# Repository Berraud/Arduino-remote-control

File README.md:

# Arduino-remote-control
Arduino based multi channel remote control for aeromodelism with telemetry and PS2 controller.
Based on arduino pro mini and NRF20L01 modules. Uses a PS2 remote controller as input.
Features multiple channels and memory for saving multiple models. Dual rates, throttle cut, on-fly default position set up (in case of signal lost), telemetry for measuring remote battery voltage and some other things.
If you have any questions email me to simonb2230@gmail.com

Based on a few nice projects from:
http://www.billporter.info/2010/06/05/playstation-2-controller-arduino-library-v1-0/
https://www.flitetest.com/articles/custom-arduino-2-4ghz-rc-transmitter
http://www.electronoobs.com/eng_robotica_tut5_2_1.php

and probably some other examples that I can't remember.

The power for the remote is from a single LiIon battery from a portable charger (using the same charging circuit)
The power for the receiver comes from the BEC of the ESC. The resistive divider on the receiver is calculated for a 3S Lipo battery.

The NRF modules need a 1uf ceramic SMD cap soldered directly on the PCB of the module itself

The range tested on ground is about 800m

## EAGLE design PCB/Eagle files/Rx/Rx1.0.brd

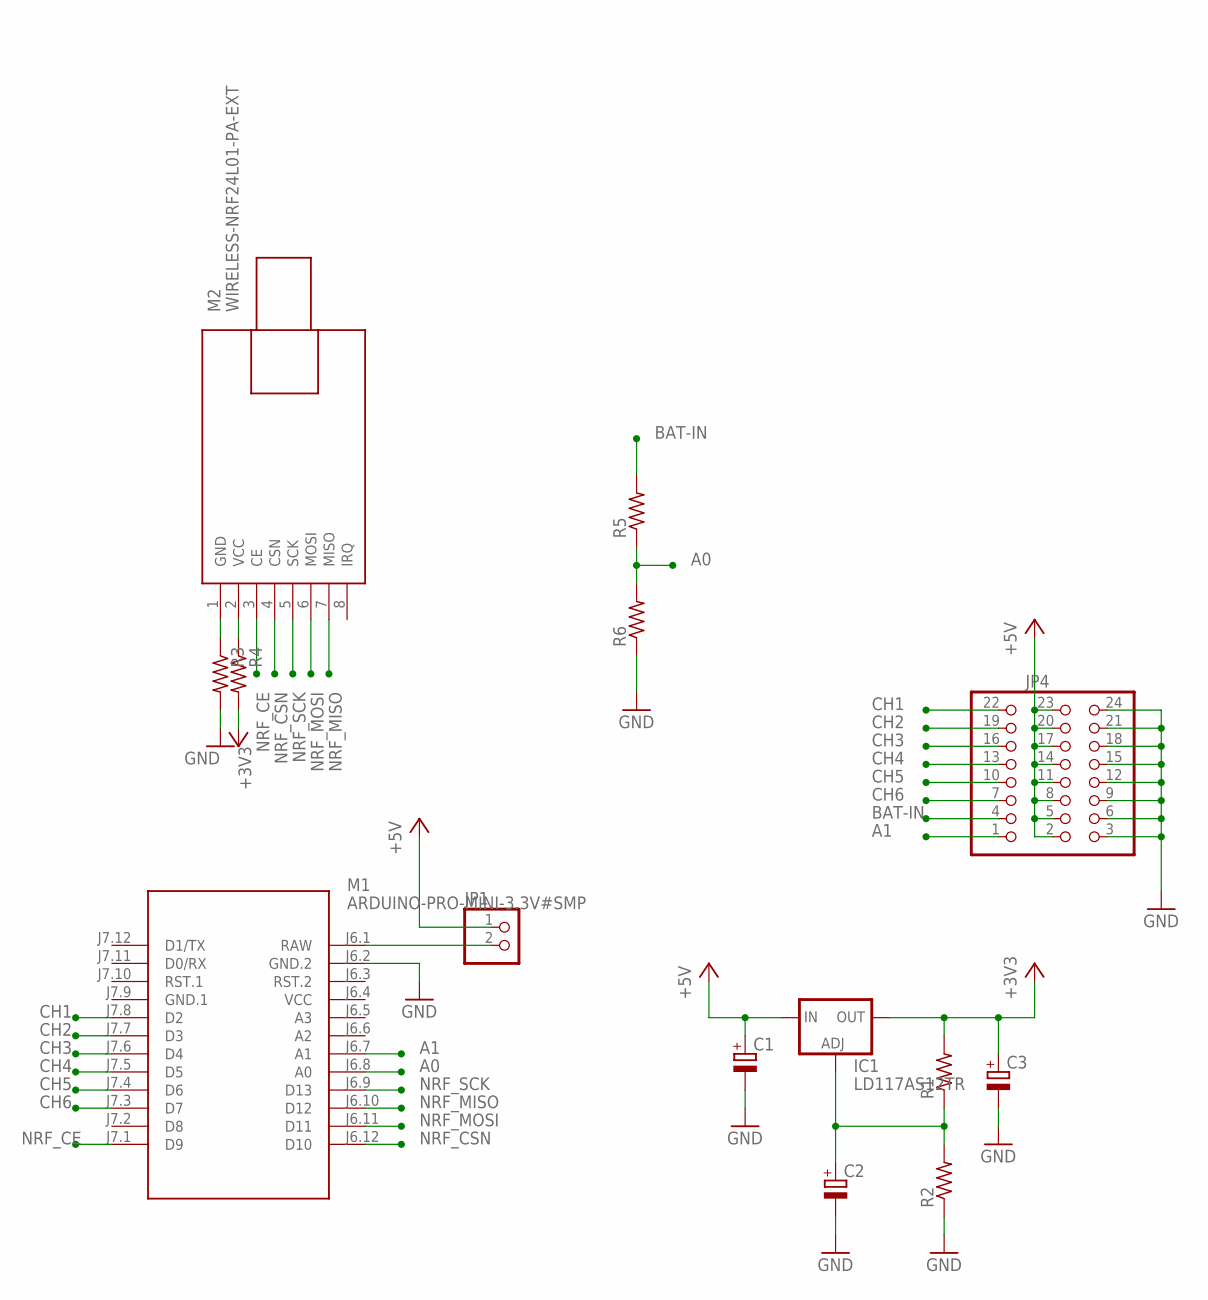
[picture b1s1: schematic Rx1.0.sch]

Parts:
C1, C2, C3: CPOL-EUE1.8-4; E1,8-4
IC1: LD117AS12TR; SOT223
JP1: PINHD-1X2; 1X02
JP4: PINHD-3X8; 2X08
M1: ARDUINO-PRO-MINI-3.3V#SMP; ARDUINO-PRO-MINI#SMP
M2: WIRELESS-NRF24L01-PA-EXT
R1, R2, R3, R4, R5, R6: R-US_0204/2V; 0204V

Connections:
+3V3: C3.+, IC1.4 (OUT), R1.2, R4.2
+5V: C1.+, IC1.3 (IN), JP1.1, JP4.2, JP4.5, JP4.8, JP4.11, JP4.14, JP4.17, JP4.20, JP4.23
A0: M1.J6.8 (A0), R5.1, R6.2
A1: JP4.1, M1.J6.7 (A1)
BAT-IN: JP4.4, R5.2
CH1: JP4.22, M1.J7.8 (D2)
CH2: JP4.19, M1.J7.7 (D3)
CH3: JP4.16, M1.J7.6 (D4)
CH4: JP4.13, M1.J7.5 (D5)
CH5: JP4.10, M1.J7.4 (D6)
CH6: JP4.7, M1.J7.3 (D7)
GND: C1.-, C2.-, C3.-, JP4.3, JP4.6, JP4.9, JP4.12, JP4.15, JP4.18, JP4.21, JP4.24, M1.J6.2 (GND.2), R2.1, R3.2, R6.1
GND.1: M1.J7.9 (GND.1)
unnamed: M2.1 (GND), R3.1
unnamed: M2.2 (VCC), R4.1
unnamed: C2.+, IC1.1 (ADJ), R1.1, R2.2
unnamed: JP1.2, M1.J6.1 (RAW)
NRF_CE: M1.J7.1 (D9), M2.3 (CE)
NRF_CSN: M1.J6.12 (D10), M2.4 (CSN)
NRF_MISO: M1.J6.10 (D12), M2.7 (MISO)
NRF_MOSI: M1.J6.11 (D11), M2.6 (MOSI)
NRF_SCK: M1.J6.9 (D13), M2.5 (SCK)
VCC: M1.J6.4 (VCC)

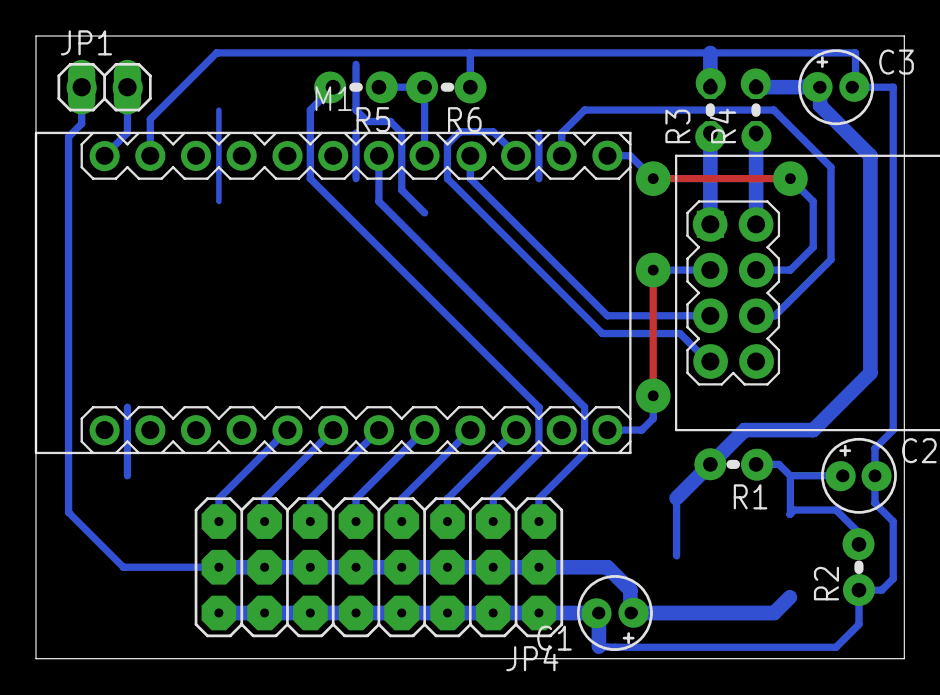
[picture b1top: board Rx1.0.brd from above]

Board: 2 copper layers, 48.2 x 34.6 mm, 14 parts (1 on the bottom side), 21 nets.

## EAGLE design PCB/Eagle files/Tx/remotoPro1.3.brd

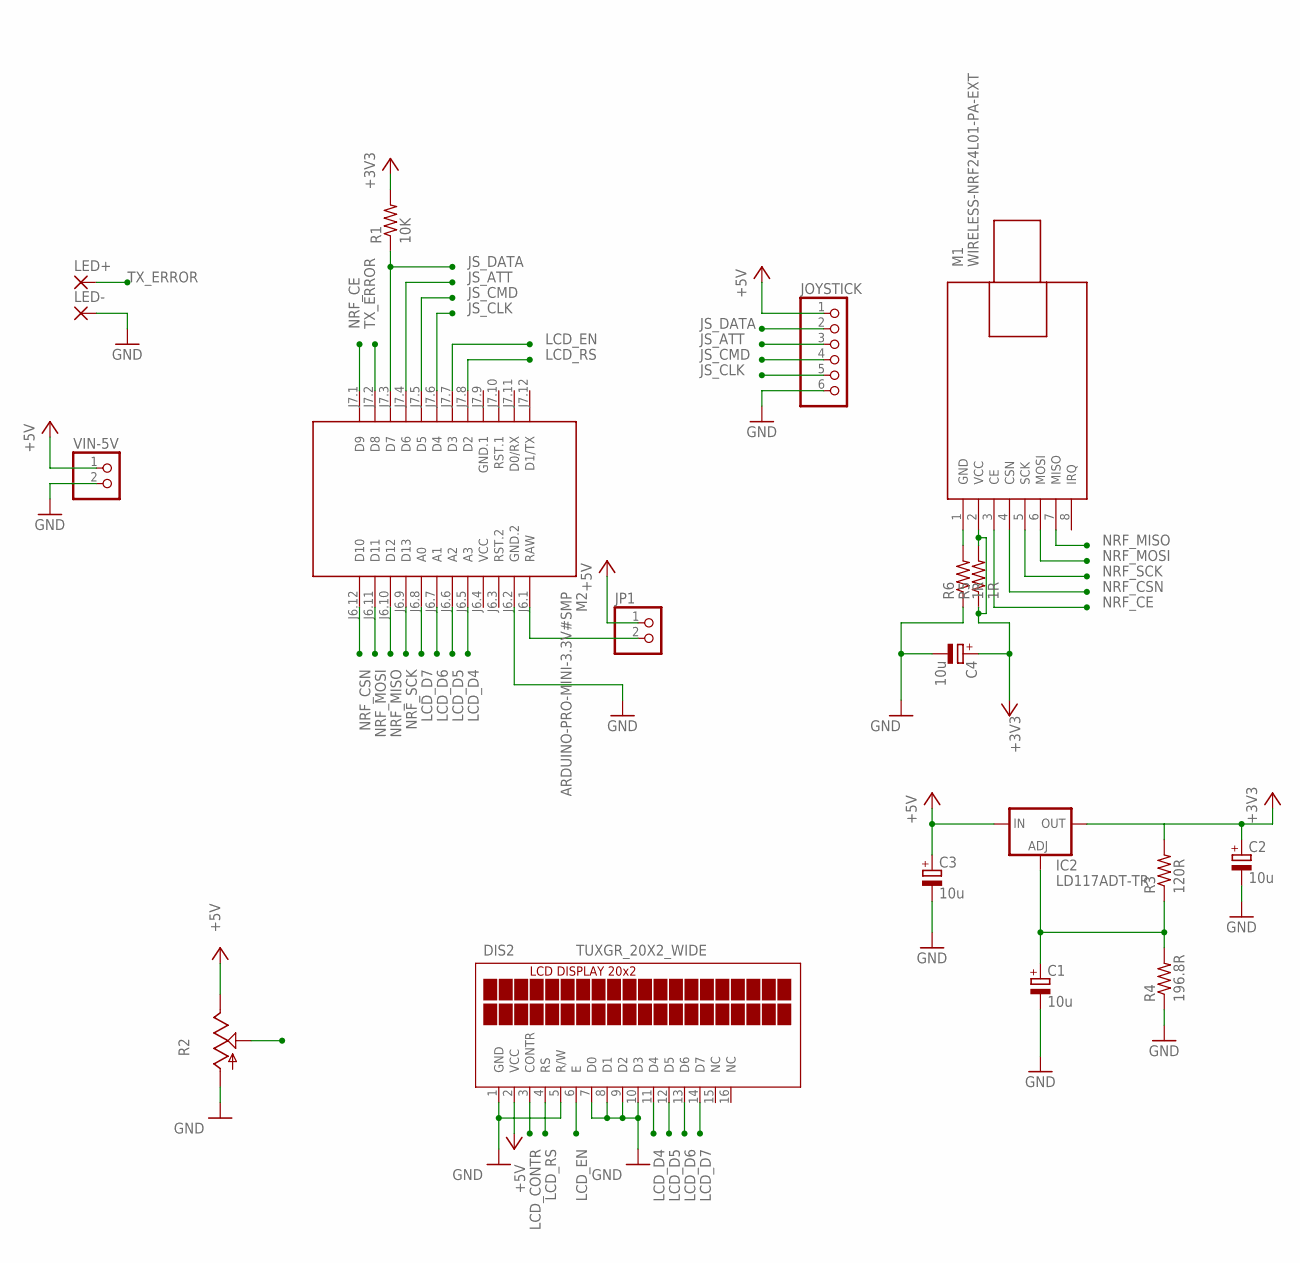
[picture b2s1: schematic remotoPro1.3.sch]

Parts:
C1, C2, C3, C4: 10u; E1,8-4
DIS2: TUXGR_20X2_WIDE
IC2: LD117ADT-TR; DPACK
JOYSTICK: PINHD-1X6; 1X06
JP1: PINHD-1X2; 1X02
LED+: 1,6/0,8
LED-: 1,6/0,8
M1: WIRELESS-NRF24L01-PA-EXT
M2: ARDUINO-PRO-MINI-3.3V#SMP; ARDUINO-PRO-MINI#SMP
R1: 10K; 0204/7
R2: TRIM_US-S75P; S75P
R3: 120R; 0204/7
R4: 196.8R; 0204/7
R5, R6: 1R; 0207/2V
VIN-5V: PINHD-1X2; 1X02

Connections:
+3V3: C2.+, C4.+, IC2.4 (OUT), M1.2 (VCC), R1.2, R3.2, R5.1, R5.2
+5V: C3.+, DIS2.2 (VCC), IC2.3 (IN), JOYSTICK.1, JP1.1, R2.E, VIN-5V.1
GND: C1.-, C2.-, C3.-, C4.-, DIS2.1 (GND), DIS2.5 (R/W), DIS2.7 (D0), DIS2.8 (D1), DIS2.9 (D2), DIS2.10 (D3), JOYSTICK.6, LED-.1, M2.J6.2 (GND.2), R2.A, R4.1, R6.1, VIN-5V.2
GND.1: M2.J7.9 (GND.1)
JS_ATT: JOYSTICK.3, M2.J7.4 (D6)
JS_CLK: JOYSTICK.5, M2.J7.6 (D4)
JS_CMD: JOYSTICK.4, M2.J7.5 (D5)
JS_DATA: JOYSTICK.2, M2.J7.3 (D7), R1.1
LCD_CONTR: DIS2.3 (CONTR), R2.S
LCD_D4: DIS2.11 (D4), M2.J6.5 (A3)
LCD_D5: DIS2.12 (D5), M2.J6.6 (A2)
LCD_D6: DIS2.13 (D6), M2.J6.7 (A1)
LCD_D7: DIS2.14 (D7), M2.J6.8 (A0)
LCD_EN: DIS2.6 (E), M2.J7.7 (D3)
LCD_RS: DIS2.4 (RS), M2.J7.8 (D2)
unnamed: JP1.2, M2.J6.1 (RAW)
unnamed: C1.+, IC2.1 (ADJ), R3.1, R4.2
unnamed: M1.1 (GND), R6.2
NRF_CE: M1.3 (CE), M2.J7.1 (D9)
NRF_CSN: M1.4 (CSN), M2.J6.12 (D10)
NRF_MISO: M1.7 (MISO), M2.J6.10 (D12)
NRF_MOSI: M1.6 (MOSI), M2.J6.11 (D11)
NRF_SCK: M1.5 (SCK), M2.J6.9 (D13)
TX_ERROR: LED+.1, M2.J7.2 (D8)
VCC: M2.J6.4 (VCC)

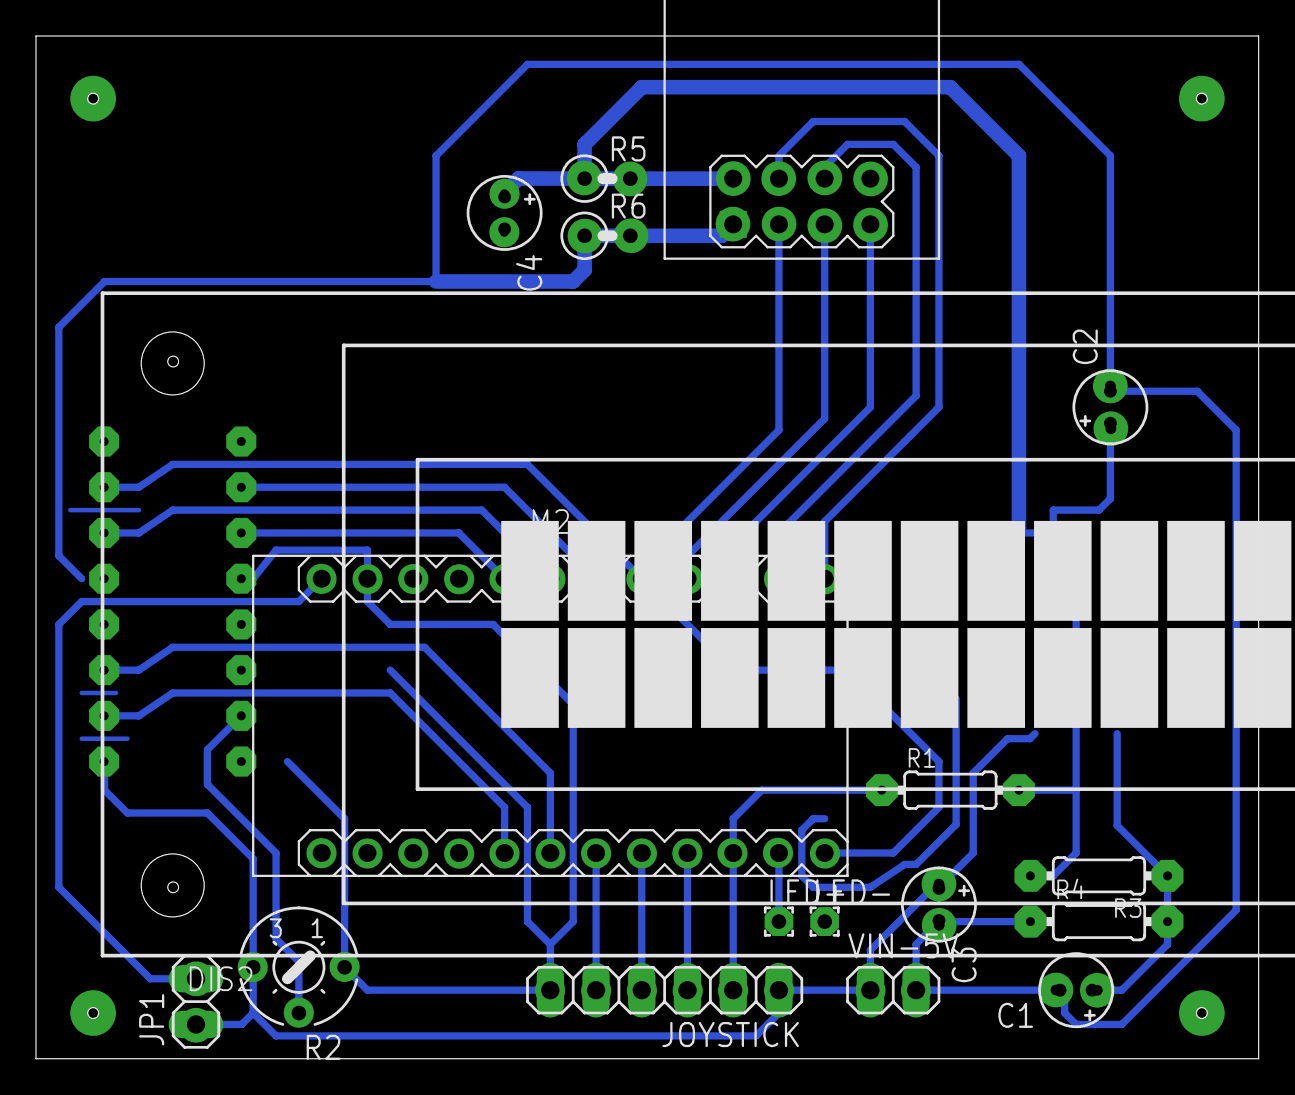
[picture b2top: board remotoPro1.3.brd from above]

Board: 2 copper layers, 67.9 x 56.8 mm, 19 parts (1 on the bottom side), 23 nets.

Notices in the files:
parts and their libraries:
diy-modules: Released under the Creative Commons Attribution 4.0 International License: http://creativecommons.org/licenses/by/4.0
